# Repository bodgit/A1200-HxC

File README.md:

# A1200-HxC

This is a simple button extender for the popular HxC floppy emulator.

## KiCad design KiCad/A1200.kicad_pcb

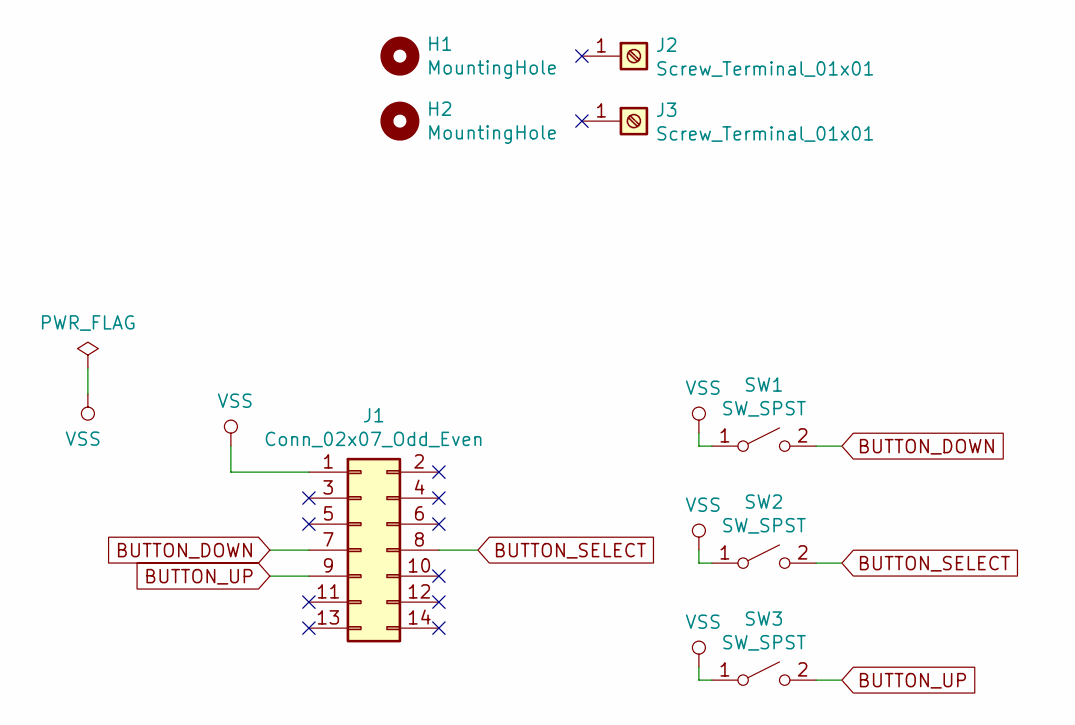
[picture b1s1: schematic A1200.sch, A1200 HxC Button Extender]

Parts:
H1, H2: MountingHole; MountingHole_3.5mm
J1: Conn_02x07_Odd_Even; PinHeader_2x07_P2.54mm_Vertical
J2, J3: Screw_Terminal_01x01; Tapped Terminal
SW1, SW2, SW3: SW_SPST; SW_PUSH_6mm_H9.5mm

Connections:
BUTTON_DOWN: J1.7, SW1.2 (B)
BUTTON_SELECT: J1.8, SW2.2 (B)
BUTTON_UP: J1.9, SW3.2 (B)
VSS: J1.1, SW1.1 (A), SW2.1 (A), SW3.1 (A)

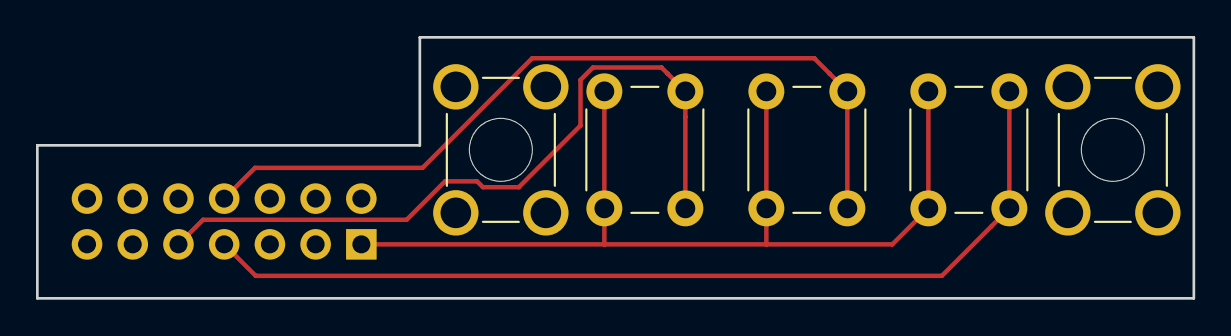
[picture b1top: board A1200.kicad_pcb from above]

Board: 2 copper layers, 64.2 x 14.5 mm, 8 parts (1 on the bottom side), 4 nets.

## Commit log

2019-04-19 Add photos
2019-04-19 Update README with photos
